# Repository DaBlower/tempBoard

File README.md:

# TempBoard
 <br/>
A PCB that shows temperature and relative humidity on a 128x64px OLED screen using a SHTC3 sensor

## Features
- An SHTC3 temperature and relative humidity sensor gets data about temperature and relative humidity
- OLED display that shows the data
- Indicator LEDs that light up when the temperature or humidity gets extreme
- A XIAO RP2040 microcontroller

## Files
To program the XIAO RP2040, follow [this guide](https://wiki.seeedstudio.com/XIAO-RP2040-with-Arduino/) and open [this file](/firmware/tempBoard/tempBoard.ino) in the Arduino IDE.

## Schematic

## PCB

## BOM
* 1 100nf capacitor
* 2 4.7 k ohm resistors
* 2 220 ohm resistors
* 1 Blue LED
* 1 Red LED
* 1 SHTC3 Temperature and humidity sensor
* 1 128x64 px OLED display
* 1 XIAO RP2040

made by ```@obob``` on the Hack Club Slack for the Hermes YSWS! (hermes.hackclub.com)

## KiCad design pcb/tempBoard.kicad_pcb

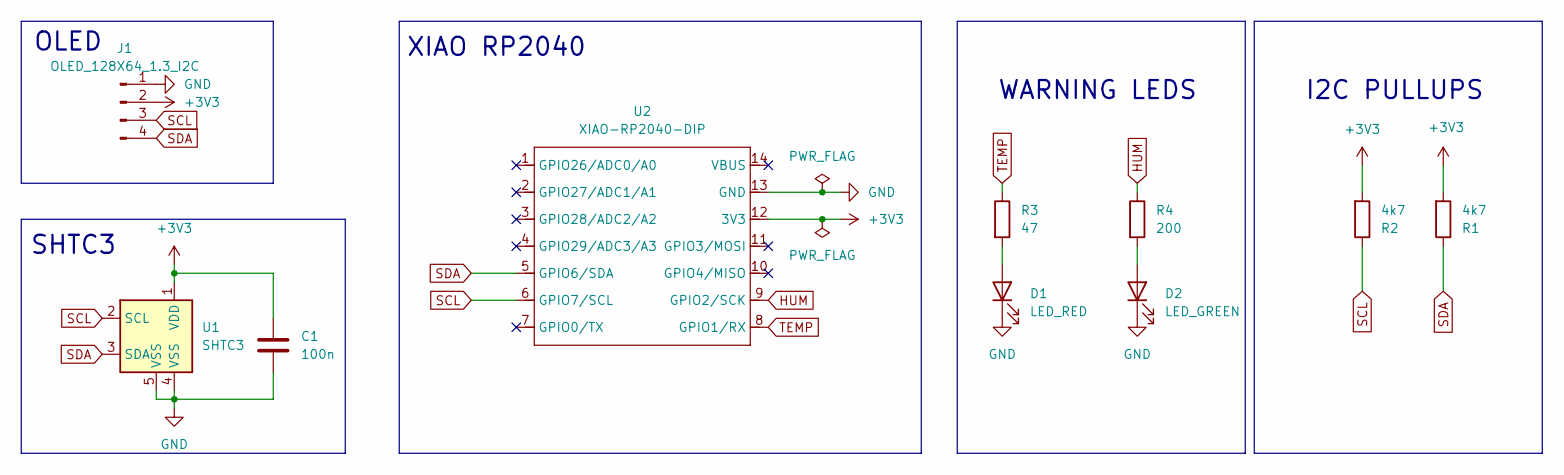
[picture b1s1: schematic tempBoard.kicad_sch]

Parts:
C1: 100n; C_0805_2012Metric
D1: LED_RED; LED_0805_2012Metric
D2: LED_GREEN; LED_0805_2012Metric
J1: OLED_128X64_1.3_I2C; 128x64OLED
R1, R2: 4k7; R_0805_2012Metric
R3: 47; R_0805_2012Metric
R4: 200; R_0805_2012Metric
U1: SHTC3; Sensirion_DFN-4-1EP_2x2mm_P1mm_EP0.7x1.6mm
U2: XIAO-RP2040-DIP

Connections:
+3V3: C1.1, J1.2, R1.2, R2.2, U1.1 (VDD), U2.12 (3V3)
GND: C1.2, D1.1 (K), D2.1 (K), J1.1, U1.4 (VSS), U1.5 (VSS), U2.13 (GND)
HUM: R4.1, U2.9 (GPIO2/SCK)
unnamed: D1.2 (A), R3.2
unnamed: D2.2 (A), R4.2
SCL: J1.3, R2.1, U1.2 (SCL), U2.6 (GPIO7/SCL)
SDA: J1.4, R1.1, U1.3 (SDA), U2.5 (GPIO6/SDA)
TEMP: R3.1, U2.8 (GPIO1/RX)

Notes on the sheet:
OLED
WARNING LEDS
SHTC3
XIAO RP2040
I2C PULLUPS

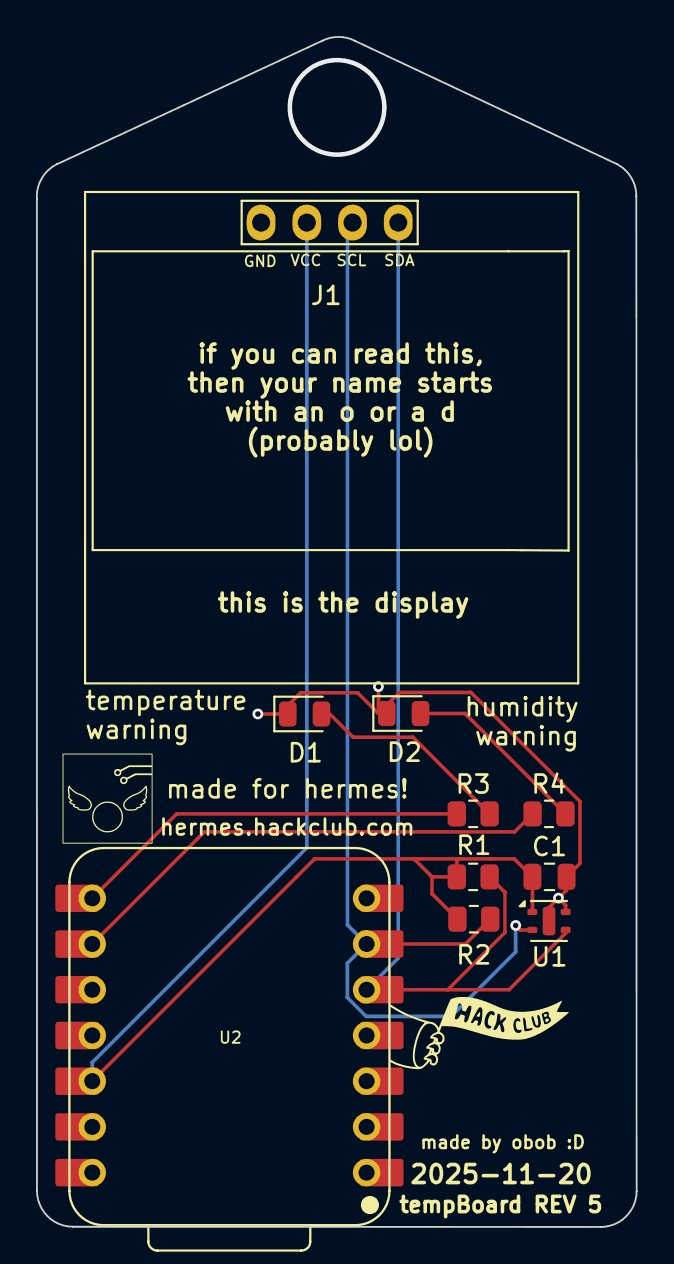
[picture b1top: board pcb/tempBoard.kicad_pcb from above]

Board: 2 copper layers, 33.3 x 66.1 mm, 10 parts (0 on the bottom side), 8 nets.

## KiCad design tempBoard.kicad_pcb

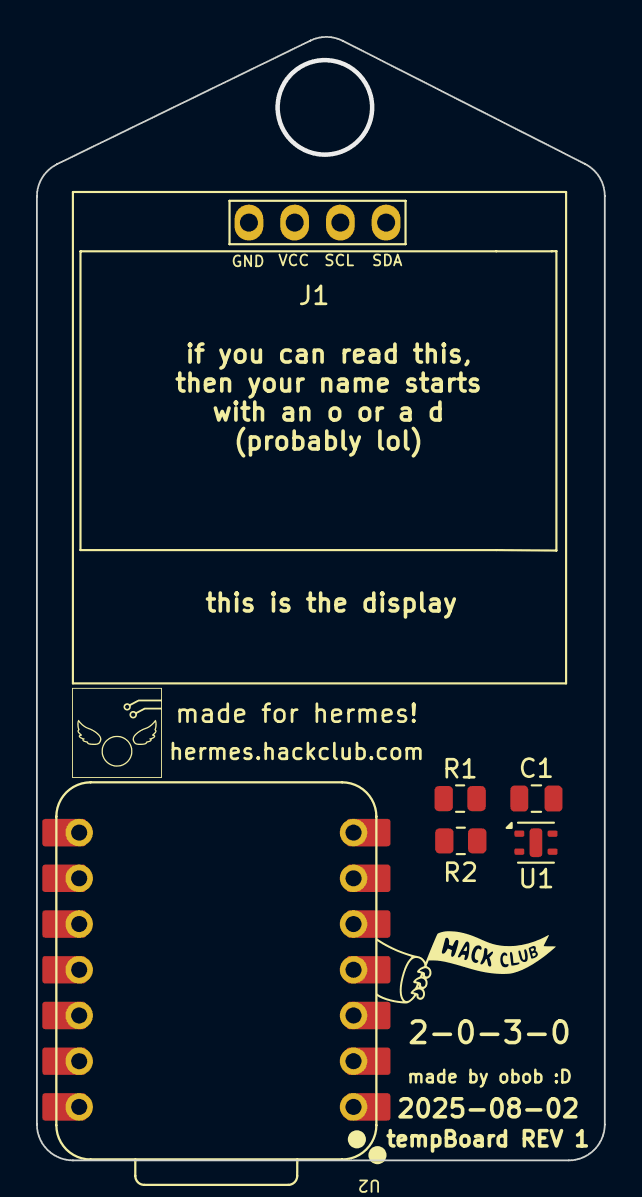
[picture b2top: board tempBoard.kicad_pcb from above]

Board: 2 copper layers, 31.6 x 62.4 mm, 6 parts (0 on the bottom side), 4 nets, no tracks yet.

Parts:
C1: 100n; C_0805_2012Metric
J1: OLED_128X64_1.3_I2C; 128x64OLED
R1, R2: R; R_0805_2012Metric
U1: SHTC3; Sensirion_DFN-4-1EP_2x2mm_P1mm_EP0.7x1.6mm
U2: XIAO-RP2040-DIP

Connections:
+3V3: C1.1, J1.2, R1.1, R2.2, U1.1 (VDD), U2.12 (3V3)
GND: C1.2, J1.1, U1.4 (VSS), U2.13 (GND)
SCL: J1.3, R2.1, U1.2 (SCL), U2.6 (GPIO7/SCL)
SDA: J1.4, R1.2, U1.3 (SDA), U2.5 (GPIO6/SDA)

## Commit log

2025-07-26 kicad init + add sensor
2025-07-26 add sensor to symbol and footprint libraries
2025-07-26 finish pcb
2025-07-26 add edge cuts
2025-08-01 add silkscreen
2025-08-02 first firmware version
2025-08-02 fixed some bugs
2025-08-02 remake pcb
2025-08-02 restructure directory
2025-08-02 added indicator lights
2025-08-02 change location of readme
2025-08-02 update image sizes
2025-08-02 add production files
2025-08-02 slight change
2025-08-03 remake production files + lcsc part number fields
2025-08-03 update production files
2025-08-03 regenerate ibom with oled and rp2040
2025-08-03 fix some dfm errors
2025-10-27 update pullups
2025-11-20 make jlc cheaper
2025-11-20 fix silkscreen
